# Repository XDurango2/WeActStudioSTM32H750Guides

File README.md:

# WeActStudio MiniSTM32H7xx – User Guides & Examples

This repository contains a collection of guides and documentation for using the **WeActStudio MiniSTM32H7xx** board, including:

- Flashing the OpenMV firmware  
- Using the board with Arduino IDE  
- Driving the WeActStudio ST7735 display under OpenMV  
- Example scripts and helper files

These guides are intended to simplify development for users working with the STM32H7-based WeActStudio boards.

---

## Included Guides

### 1. Flashing OpenMV Firmware  
Learn how to download the SDK, locate the OpenMV firmware, put the board into DFU mode, and flash the `openmv.bin` file using the WeActStudio download tool.

**Guide:** [`Flashing OpenMV Firmware(Windows)`](Guides-EN/Windows/OpenMV_firmware_flash.md)
**Guide:** [`Flashing OpenMV Firmware(Linux)`](Guides-EN/Linux/OpenMV_firmware_flash.md)

---

### 2. Using the Board with Arduino IDE  
Instructions for installing STM32 board support, configuring DFU upload mode, selecting the correct board, and enabling USB CDC Serial.

**Guide:** [`Arduino IDE Setup(Windows)`](Guides-EN/Windows/Arduino_programming.md)
**Guide:** [`Arduino IDE Setup(Linux)`](Guides-EN/Linux/Arduino_programming.md)

---

### 3. Using the WeActStudio Display in OpenMV  
A detailed guide for copying the display driver scripts, using the example project, and troubleshooting incorrect color tabs for ST7735 screens.

 **Guide:** [`Using the Display in OpenMV`](Guides-EN/OpenMV_display_setup_new.md)

---

### 4. Schematics
Oh, this is New!, in this folder is a KiCad Project Based on the WeAct Board. Please This is a **proof of concept** design. It has **not been tested** in any way, shape, or form.  
These files are provided publicly **for demonstration and educational purposes only**.

**Files:** [`KiCad Project`](Schematics/Schematics_STM32H750.md)

##  Requirements

Depending on the part of the repository you use, you may need:

- **WeActStudio MiniSTM32H7xx board**
- **WeActStudio ST7735 display** (80×160, 128×128, or variant)
- **OpenMV IDE**
- **Arduino IDE 2.x**
- **STM32CubeProgrammer**
- USB-C cable capable of data transfer

---

## 🔗 Useful Links

- WeActStudio GitHub: https://github.com/WeActStudio/MiniSTM32H7xx  
- STM32 Arduino Core: https://github.com/stm32duino  
- OpenMV: https://openmv.io  
- STM32CubeProgrammer: https://www.st.com/en/development-tools/stm32cubeprog.html  

---

## Guías en Español

### 1. Flashear Firmware OpenMV
**Guía:** [`Flashear Firmware OpenMV (Windows)`](Guides-ES/Windows/Flasheo_Firmware_OpenMV.md)
**Guía:** [`Flashear Firmware OpenMV (Linux)`](Guides-ES/Linux/Flasheo_Firmware_OpenMV.md)

---

### 2. Programar con Arduino IDE
**Guía:** [`Configuración Arduino IDE (Windows)`](Guides-ES/Windows/Arduino_IDE_configuracion.md)
**Guía:** [`Configuración Arduino IDE (Linux)`](Guides-ES/Linux/Arduino_IDE_configuracion.md)

---

### 3. Usar el Display en OpenMV
**Guía:** [`Uso del Display en OpenMV`](Guides-ES/Uso_Display_OpenMV_nuevo.md)

---

## Contributing

Pull requests for improving documentation, providing code examples, or adding troubleshooting information are welcome.

---

##  Support

If this repository helps you, consider starring the repo to support its development.

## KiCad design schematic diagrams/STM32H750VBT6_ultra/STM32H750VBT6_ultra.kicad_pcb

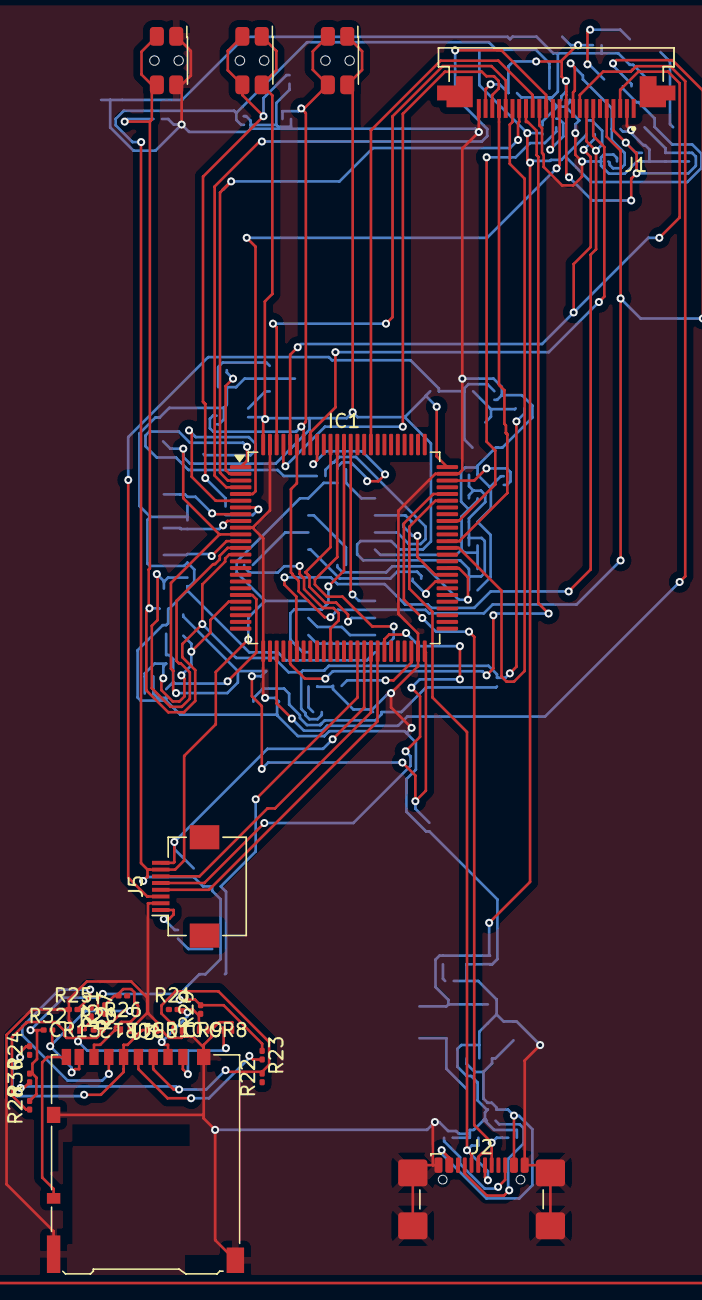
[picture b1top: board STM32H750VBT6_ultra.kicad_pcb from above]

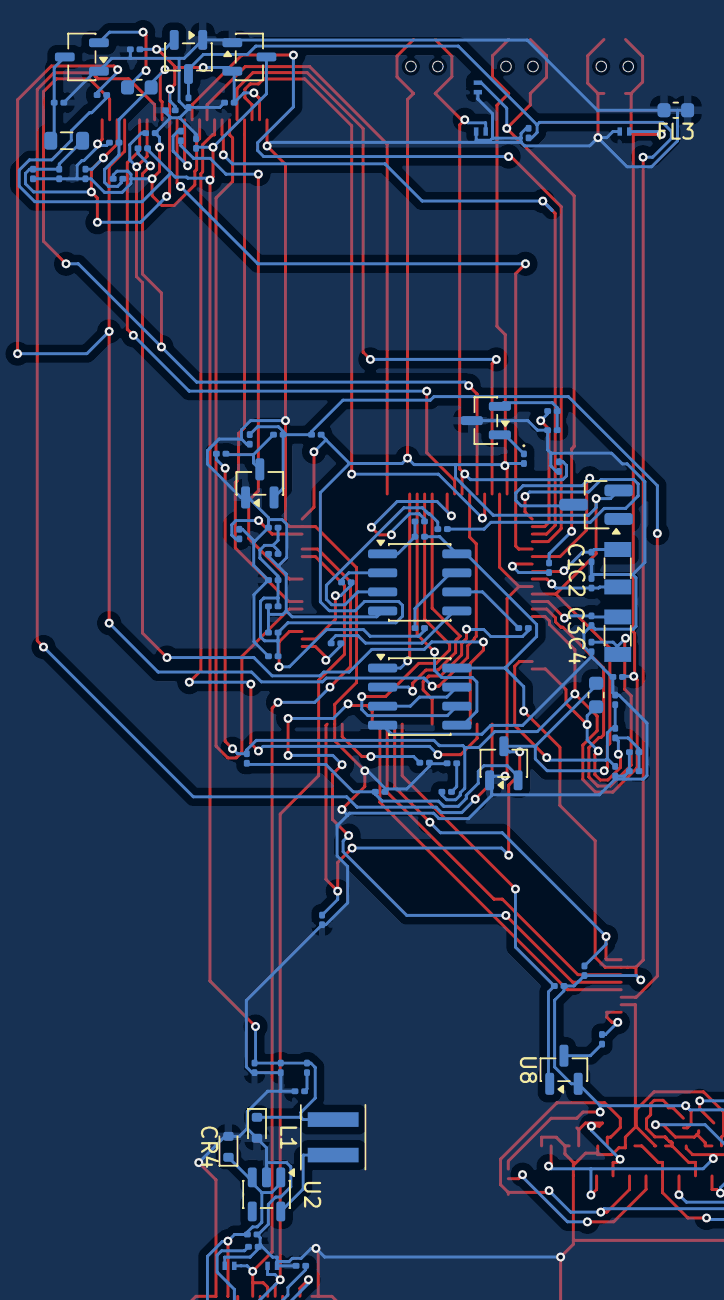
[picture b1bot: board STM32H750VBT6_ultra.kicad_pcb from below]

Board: 2 copper layers, 117 parts (90 on the bottom side), 84 nets.

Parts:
C1, C2, C3, C4, C5, C6, C7, C8, C9, C10, C11, C12, C13, C14, C15, C16, C17, C18, C19, C20, C21, C22, C23, C24, C25, C26, C27, C28, C29, C30, C31, C32, C33, C34, C35: CL10C100JB8NNNC; C_0201_0603Metric
CR1, CR2, CR3, CR6, CR7, CR8, CR9, CR10, CR11, CR12, CR13: SP0402B-ULC-01ETG; SP0402_LTF
CR4, CR5: LESD5Z5.0CT1G; D_SOD-523
D1: BAT54C-7-F; SOT-23_Handsoldering
D2: APT1608QBC_D; LED_0201_0603Metric
FL1, FL2, FL3: MMZ1608Y102BTA00; L_0603_1608Metric
IC1: STM32H750VBT6; LQFP-100_14x14mm_P0.5mm
J1: SFV24R-3STBE1HLF; AMPHENOL_SFV24R-3STBE1HLF
J2: USB_C_Receptacle_USB2.0_16P; USB_C_Receptacle_GCT_USB4110
J3: Micro_SD_Card_Det_Hirose_DM3AT; microSD_HC_Hirose_DM3AT-SF-PEJM5
J5: 5051100892; Hirose_FH12-8S-0.5SH_1x08-1MP_P0.50mm_Horizontal
L1: SRP4020TA-2R2M; L_Coilcraft_XxL4020
L2: MLZ2012M100W; L_0805_2012Metric
Q1: MMBT3906; SOT-23
Q2: BC857; SOT-23
R1, R2, R3, R4, R5, R6, R7, R8, R9, R10, R11, R12, R13, R14, R15, R16, R17, R18, R19, R20, R21, R22, R23, R24, R25, R26, R27, R28, R29, R30, R31, R32, R33, R34, R35, R36, R37, R38, R39, R40, R41, R42: R; R_0201_0603Metric
SW1, SW2, SW3: SW_Push; SW_SPST_EVQP7C
U1: MAX809TEUR_T; SOT-23-3
U2: AP2112K-3.3; SOT-23-5
U3, U7: W25Q64JVSSIQ; SOIC-8_3.9x4.9mm_P1.27mm
U4, U5, U6: PMIC-LDO-XC6206P332MR-G_SOT23_; SOT-23-3
U8: SI2301CDS-T1-GE3; SOT-23
Y1: ABS05-32.768KHZ-7-T; Crystal_SMD_3215-2Pin_3.2x1.5mm
Y2: ABM3-25.000MHZ-D2Y-T; Crystal_SMD_3215-2Pin_3.2x1.5mm

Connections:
+1V5: C28.2, C29.2, FL2.1, J1.10
+2V8: C25.2, C26.2, C31.2, C32.2, C33.2, C34.2, J1.4, J1.11, J1.23, L2.1, U4.2 (VOUT), U6.2 (VOUT)
+3.3V: C22.2, C23.2, C30.2, CR5.1, L1.2, R12.2, R17.1, R18.1, U6.3 (VIN)
+3V3: C24.2, C35.2, J5.7, R23.1, R28.2, R29.2, R30.2, R31.1, R32.1, R39.2, R40.1, R41.2, U3.8 (VCC), U4.3 (VIN), U7.8 (VCC), U8.2 (S)
/0.96'' TFT-LCD/LCD_LEDA: J5.1, R42.1
/DVP_PWDN: IC1.31 (PA7), J1.8, R19.2
/LCD_CS: IC1.41 (PE11), J5.8, R40.2
/LCD_LED: IC1.40 (PE10), R41.1, U8.1 (G)
/LCD_RESET: C18.2, J5.3, Q1.2 (E), R7.1, R8.2
/LCD_SCL: IC1.42 (PE12), J5.6
/LCD_SDA: IC1.44 (PE14), J5.5
/LCD_WR_RS: IC1.43 (PE13), J5.4
/MicroSD/MicroSD_SW: J3.9 (DET_B), J3.10 (DET_A)
/QSPI_BK1_IO0: IC1.58 (PD11), R38.2
/QSPI_BK1_IO1: IC1.59 (PD12), R34.1
/QSPI_BK1_IO2: IC1.1 (PE2), R35.1
/QSPI_BK1_IO3: IC1.60 (PD13), R36.2
/QSPI_BK1_NCS: IC1.92 (PB6), R33.1
/QSPI_CLK: IC1.36 (PB2), R37.2
/SPIx_CLK: IC1.89 (PB3), U7.6 (CLK)
/SPIx_CS: IC1.87 (PD6), U7.1 (/CS)
/SPIx_MISO: IC1.90 (PB4), U7.2 (DO(IO1))
/SPIx_MOSI: IC1.88 (PD7), U7.5 (DI(IO0))
BOOT0: CR1.2, IC1.94 (BOOT0), R1.2, SW1.2
DCMI_D0: IC1.63 (PC6), J1.19
DCMI_D1: IC1.64 (PC7), J1.21
DCMI_D2: IC1.97 (PE0), J1.22
DCMI_D3: IC1.98 (PE1), J1.20
DCMI_D4: IC1.3 (PE4), J1.18
DCMI_D5: IC1.84 (PD3), J1.16
DCMI_D6: IC1.4 (PE5), J1.14
DCMI_D7: IC1.5 (PE6), J1.12
DCMI_HSYNC: IC1.28 (PA4), J1.9
DCMI_PIXCLK: IC1.30 (PA6), J1.17
DCMI_VSYNC: IC1.93 (PB7), J1.7
Earth: C1.1, C2.1, C3.1, C4.1, C5.1, C6.1, C7.1, C8.2, C9.2, C10.1, C11.1, C12.1, C13.1, C14.1, C15.1, C16.1, C17.1, C18.1, C19.1, C20.1, C21.1, C22.1, C23.1, C24.1, C25.1, C26.1, C27.1, C28.1, C29.1, C30.1, C31.1, C32.1, C33.1, C34.1, C35.1, CR1.1, CR2.1, CR3.1, CR4.2, CR5.2, CR6.1, CR7.1, CR8.2, CR9.2, CR10.2, CR11.1, CR12.1, CR13.1, FL3.1, FL3.2, IC1.10 (VSS_1), IC1.26 (VSS_2), IC1.49 (VSS_3), IC1.74 (VSS_4), IC1.99 (VSS_5), J1.2, J1.15, J1.24, J2.A1 (GND), J2.A12 (GND), J2.B1 (GND), J2.B12 (GND), J2.S1 (SHIELD), J3.11 (SHIELD), J5.2, Q1.1 (B), Q2.3 (C), R1.1, R6.2, R10.2, R13.1, R14.1, R15.1, R19.1, R25.1, SW3.1, U1.1 (GND), U2.2 (GND), U3.4 (GND), U4.1 (VSS), U5.1 (VSS), U6.1 (VSS), U7.4 (GND)
I2C1_SCL: IC1.95 (PB8), J1.5, R18.2
I2C1_SDA: IC1.96 (PB9), J1.3, R17.2
NRST: C5.2, CR3.2, IC1.14 (NRST), R4.1, R9.2, R11.1, SW3.2
unnamed: CR2.2, R3.1, SW2.2
unnamed: C1.2, IC1.8 (PC14-OSC32_IN), Y1.2
unnamed: C2.2, IC1.9 (PC15-OSC32_OUT), Y1.1
unnamed: C3.2, IC1.12 (PH0-OSC_IN), Y2.1
unnamed: C4.2, IC1.13 (PH1-OSC_OUT), Y2.2
unnamed: C6.2, IC1.48 (VCAP_1)
unnamed: C7.2, IC1.73 (VCAP_2)
unnamed: C8.1, C9.1, FL1.1, IC1.21 (VDDA), R2.1
unnamed: C10.2, C11.2, IC1.20 (VREF+), R2.2
unnamed: J1.13, R16.2
unnamed: CR11.2, J3.5 (CLK), R24.2
unnamed: CR10.1, J3.3 (CMD), R22.2, R30.1
unnamed: CR12.2, J3.7 (DAT0), R26.2, R31.2
unnamed: CR13.2, J3.8 (DAT1), R27.2, R32.2
unnamed: CR8.1, J3.1 (DAT2), R20.2, R28.1
unnamed: CR9.1, J3.2 (DAT3/CD), R21.2, R29.1
unnamed: J3.4 (VDD), R23.2
unnamed: J3.6 (VSS), R25.2
unnamed: Q1.3 (C), R4.2, R7.2
unnamed: D2.1, Q2.1 (B)
unnamed: Q2.2 (E), R5.2, R6.1
unnamed: R12.1, R13.2
unnamed: R9.1, R10.1, U1.2 (~RESET)
unnamed: L1.1, U2.5 (VOUT)
unnamed: R37.1, U3.6 (CLK)
unnamed: R38.1, U3.5 (DI(IO0))
unnamed: R34.2, U3.2 (DO(IO1))
unnamed: R33.2, R39.1, U3.1 (/CS)
unnamed: R36.1, U3.7 (/HOLD_OR_/RESET(IO3))
unnamed: R35.2, U3.3 (/WP(IO2))
unnamed: C27.2, L2.2, U5.3 (VIN)
unnamed: FL2.2, U5.2 (VOUT)
unnamed: U7.3 (/WP(IO2)), U7.7 (/HOLD_OR_/RESET(IO3))
unnamed: R42.2, U8.3 (D)
PC13: IC1.7 (PC13), R3.2
PE3: IC1.2 (PE3), R5.1
RCC_MCO_1: IC1.67 (PA8), R16.1
SYS_RESET: C20.2, R11.2
USB_CC1: J2.A5 (CC1), R14.2
USB_CC2: J2.B5 (CC2), R15.2
USB_DN: CR6.2, IC1.70 (PA11), J2.A7 (D-), J2.B7 (D-)
USB_DP: CR7.2, IC1.71 (PA12), J2.A6 (D+), J2.B6 (D+)
VBAT: D1.3, IC1.6 (VBAT)
VBUS: C21.2, CR4.1, J2.A4 (VBUS), J2.A9 (VBUS), J2.B4 (VBUS), J2.B9 (VBUS), U2.1 (VIN), U2.3 (EN)
VDD-MCU: C12.2, C13.2, C14.2, C15.2, C16.2, C17.2, C19.2, D1.2, D2.2, FL1.2, IC1.11 (VDD_1), IC1.50 (VDD_3), IC1.75 (VDD_4), IC1.100 (VDD_5), R8.1, SW1.1, SW2.1, U1.3 (VCC)

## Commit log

2025-11-16 Guides in English Added
2025-11-16 renaming of guides-EN
2025-11-16 README added
    This README provides comprehensive user guides and examples for the WeActStudio MiniSTM32H7xx board, covering topics like firmware flashing, Arduino IDE setup, and display usage.
2025-11-16 Add link to OpenMV firmware flashing guide
2025-11-16 changing guide names in spanish
2025-11-16 Update prerequisites with flashing guide link
    Added link to the OpenMV firmware flashing guide.
2025-11-16 Fix link case sensitivity in OpenMV guide
2025-11-16 Fix link to OpenMV display setup guide
2025-11-16 Update link to OpenMV display guide
2025-11-16 Fix link case sensitivity in README.md
2025-11-16 Fix formatting in OpenMV display setup guide
2025-11-16 Clean up README formatting
    Removed unnecessary lines in the README file.
2025-11-16 Update file path reference in display setup guide
2025-11-18 schematic diagrams
2025-11-18 READMEs added to the schematics
2025-11-19 PCB images
2025-11-26 schematic files and PCBs in Eagle
2026-05-14 agregado de Linux y division de explicaciones por SO
2026-05-14 fix de typos en guia y agregado de guía en inglés
2026-05-14 linux links added
2026-05-14 spanish guides added to the README and linux links added to other guides
2026-05-14 firmware version notes added
2026-05-14 hotfix #1: typos in model names
2026-06-03 Update display guides for firmware version changes and add new examples
2026-06-03 Update OpenMV display setup guide link
